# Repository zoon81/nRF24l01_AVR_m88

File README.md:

### Intro
This project was made as an experiment with nRF24l01+ radios.This is a powerfull and cheap wireless interface for any microcontroller project.<br />
I trying to design and make a radio controllerd r/c car.I have everything exept the controllers (receiver and transmitter).
I going to use an ATMEGA88PA micro in the trasmitter and in the receiver too.<br />
### Features
  PWM controlled speed, left/right turn, front lights<br />
  Handbreak<br />
  Out of range detection<br />
  Battery status indicator<br />
### Source code structure
  HAL       --- Hardware Abstraction Layer, low level peripherial drivers<br />
  Drivers   --- External device driver like the nRF24l01 radio<br />
  Utils     --- Everything else<br />

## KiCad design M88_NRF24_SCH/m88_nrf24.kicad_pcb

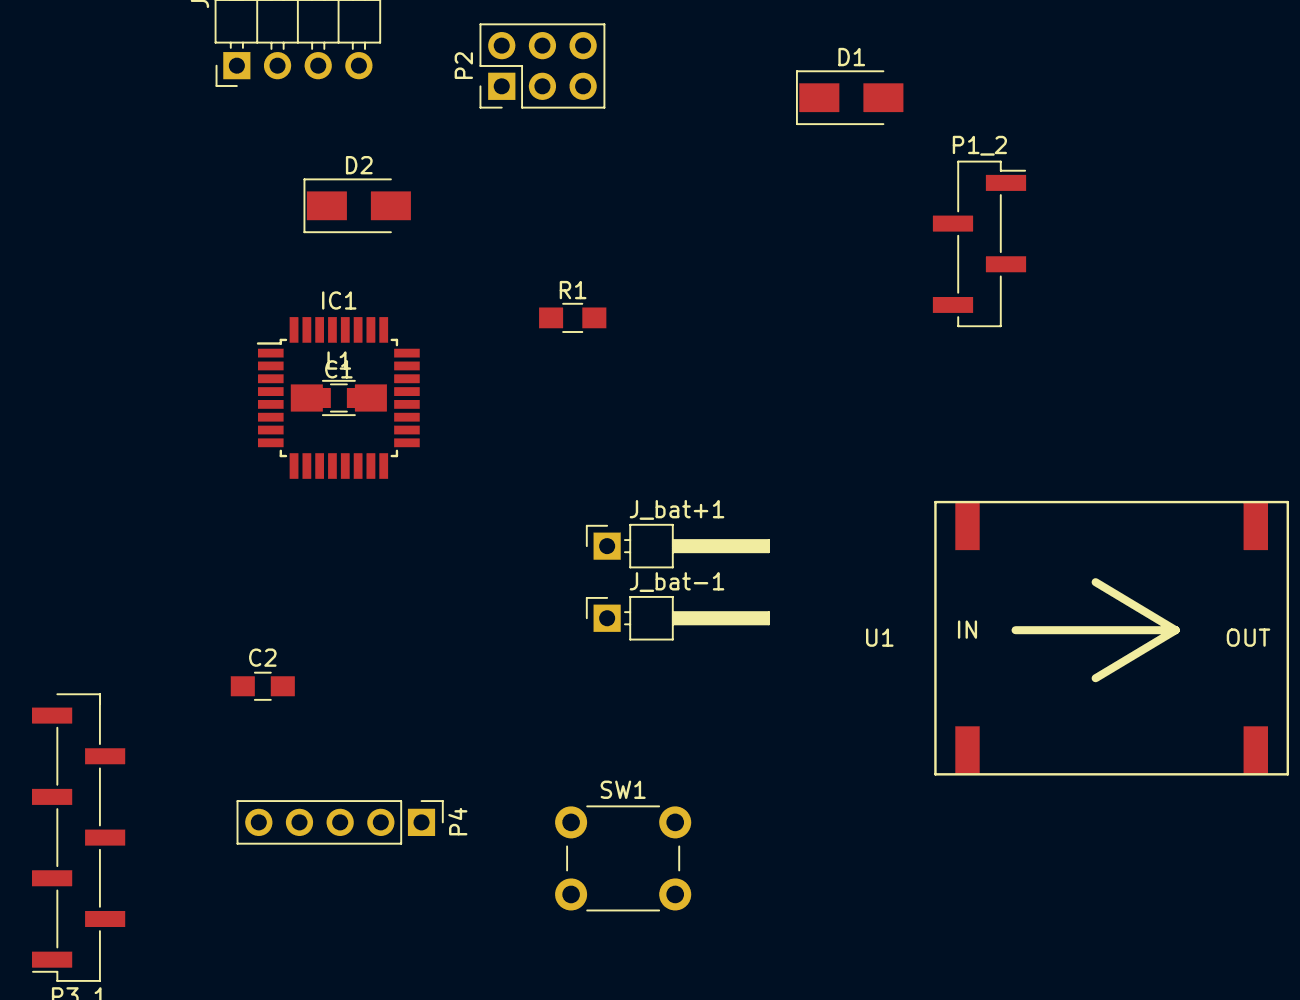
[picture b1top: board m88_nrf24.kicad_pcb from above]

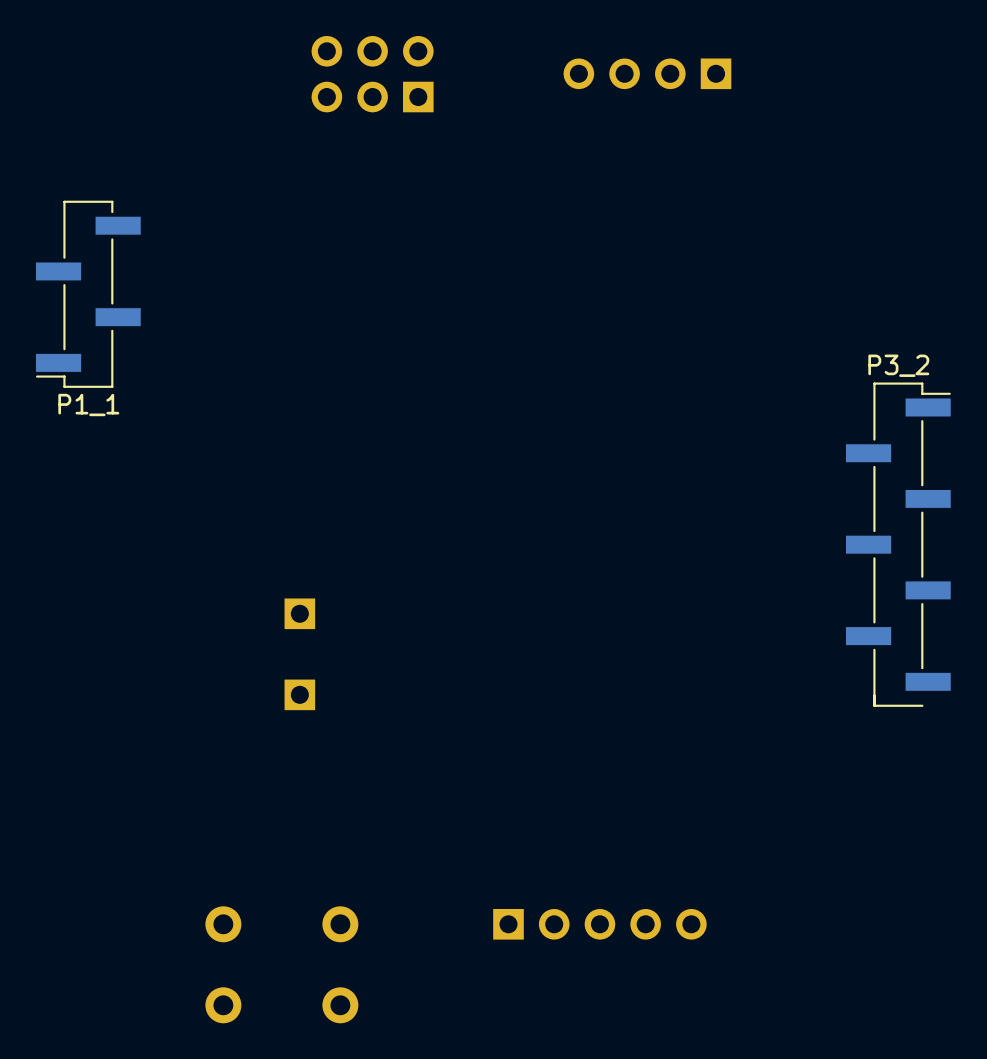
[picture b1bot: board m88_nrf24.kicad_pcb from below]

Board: 2 copper layers, 18 parts (2 on the bottom side), 28 nets, no tracks yet.

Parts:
C1: 100nF; C_0805_HandSoldering
C2: 0.1uF; C_0805_HandSoldering
D1, D2: D; D_SMA
IC1: ATMEGA88-A; TQFP-32_7x7mm_Pitch0.8mm
J5: Conn_DISP; Pin_Header_Angled_1x04_Pitch2.54mm
J_bat+1: Conn_01x01; Pin_Header_Angled_1x01_Pitch2.54mm
J_bat-1: Conn_01x01; Pin_Header_Angled_1x01_Pitch2.54mm
L1: 10uH; L_1206_HandSoldering
P1_1: NRF_CONN_P1; Pin_Header_Straight_1x04_Pitch2.54mm_SMD_Pin1Right
P1_2: NRF_CONN_P2; Pin_Header_Straight_1x04_Pitch2.54mm_SMD_Pin1Right
P2: ISP_CON; Pin_Header_Straight_2x03_Pitch2.54mm
P3_1, P3_2: Remote_CONN; Pin_Header_Straight_1x07_Pitch2.54mm_SMD_Pin1Right
P4: SERIAL_PORT; Pin_Header_Straight_1x05_Pitch2.54mm
R1: 10K; R_0805_HandSoldering
SW1: SW_DIP_x01; SW_PUSH_6mm_h13mm
U1: mp1584_module

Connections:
/ADC0: IC1.23, P3_2.4
/ADC1: IC1.24, P3_2.5
/ADC6: IC1.19, P3_1.7
/ADC7: IC1.22, P3_1.1
/DTR: C2.2, P4.4
/GPIO_PB0: IC1.12, P1_1.2
/GPIO_PB1: IC1.13, P1_2.2
/GPIO_PB7: IC1.8, P3_1.2
/GPIO_PC2: IC1.25, P3_2.2
/GPIO_PC3: IC1.26, P3_2.1
/GPIO_PD2_INT0: IC1.32, P1_2.4
/GPIO_PD4: IC1.2, P3_1.6
/GPIO_PD5: IC1.9, P3_1.5
/GPIO_PD6: IC1.10, P3_1.3, P3_1.4
/I2C_SCL: IC1.28, J5.3
/I2C_SDA: IC1.27, J5.2
/ISP_MISO: IC1.15, P1_2.3, P2.1
/ISP_MOSI: IC1.16, P1_1.4, P2.4
/ISP_SCK: IC1.17, P1_1.3, P2.3
/MCU_RESET: C2.1, IC1.29, P2.5, R1.2, SW1.1
/RXD: IC1.30, P4.3
/TXD: IC1.31, P4.2
/VCC_ISP: D1.2, P2.2
/VCC_SER: D2.2, P4.1
GND: C1.2, IC1.3, IC1.5, IC1.21, J5.4, J_bat-1.1, P1_1.1, P2.6, P3_2.6, P4.5, SW1.2, U1.1, U1.3
unnamed: C1.1, IC1.18, IC1.20, L1.1
unnamed: J_bat+1.1, U1.2
VCC: D1.1, D2.1, IC1.4, IC1.6, J5.1, L1.2, P1_2.1, P3_2.7, R1.1, U1.4

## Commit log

2017-10-16 makefile polishing
2017-10-19 Huge Update
2017-10-20 remote_controller integration testing, nonblocking adc conversation, radio communication package definition
2017-10-21 Project structure rebase
2017-11-01 Initial Schemtic added
2017-11-03 Updated schematic
2017-12-03 Transmitter working
2017-12-05 Polishing
